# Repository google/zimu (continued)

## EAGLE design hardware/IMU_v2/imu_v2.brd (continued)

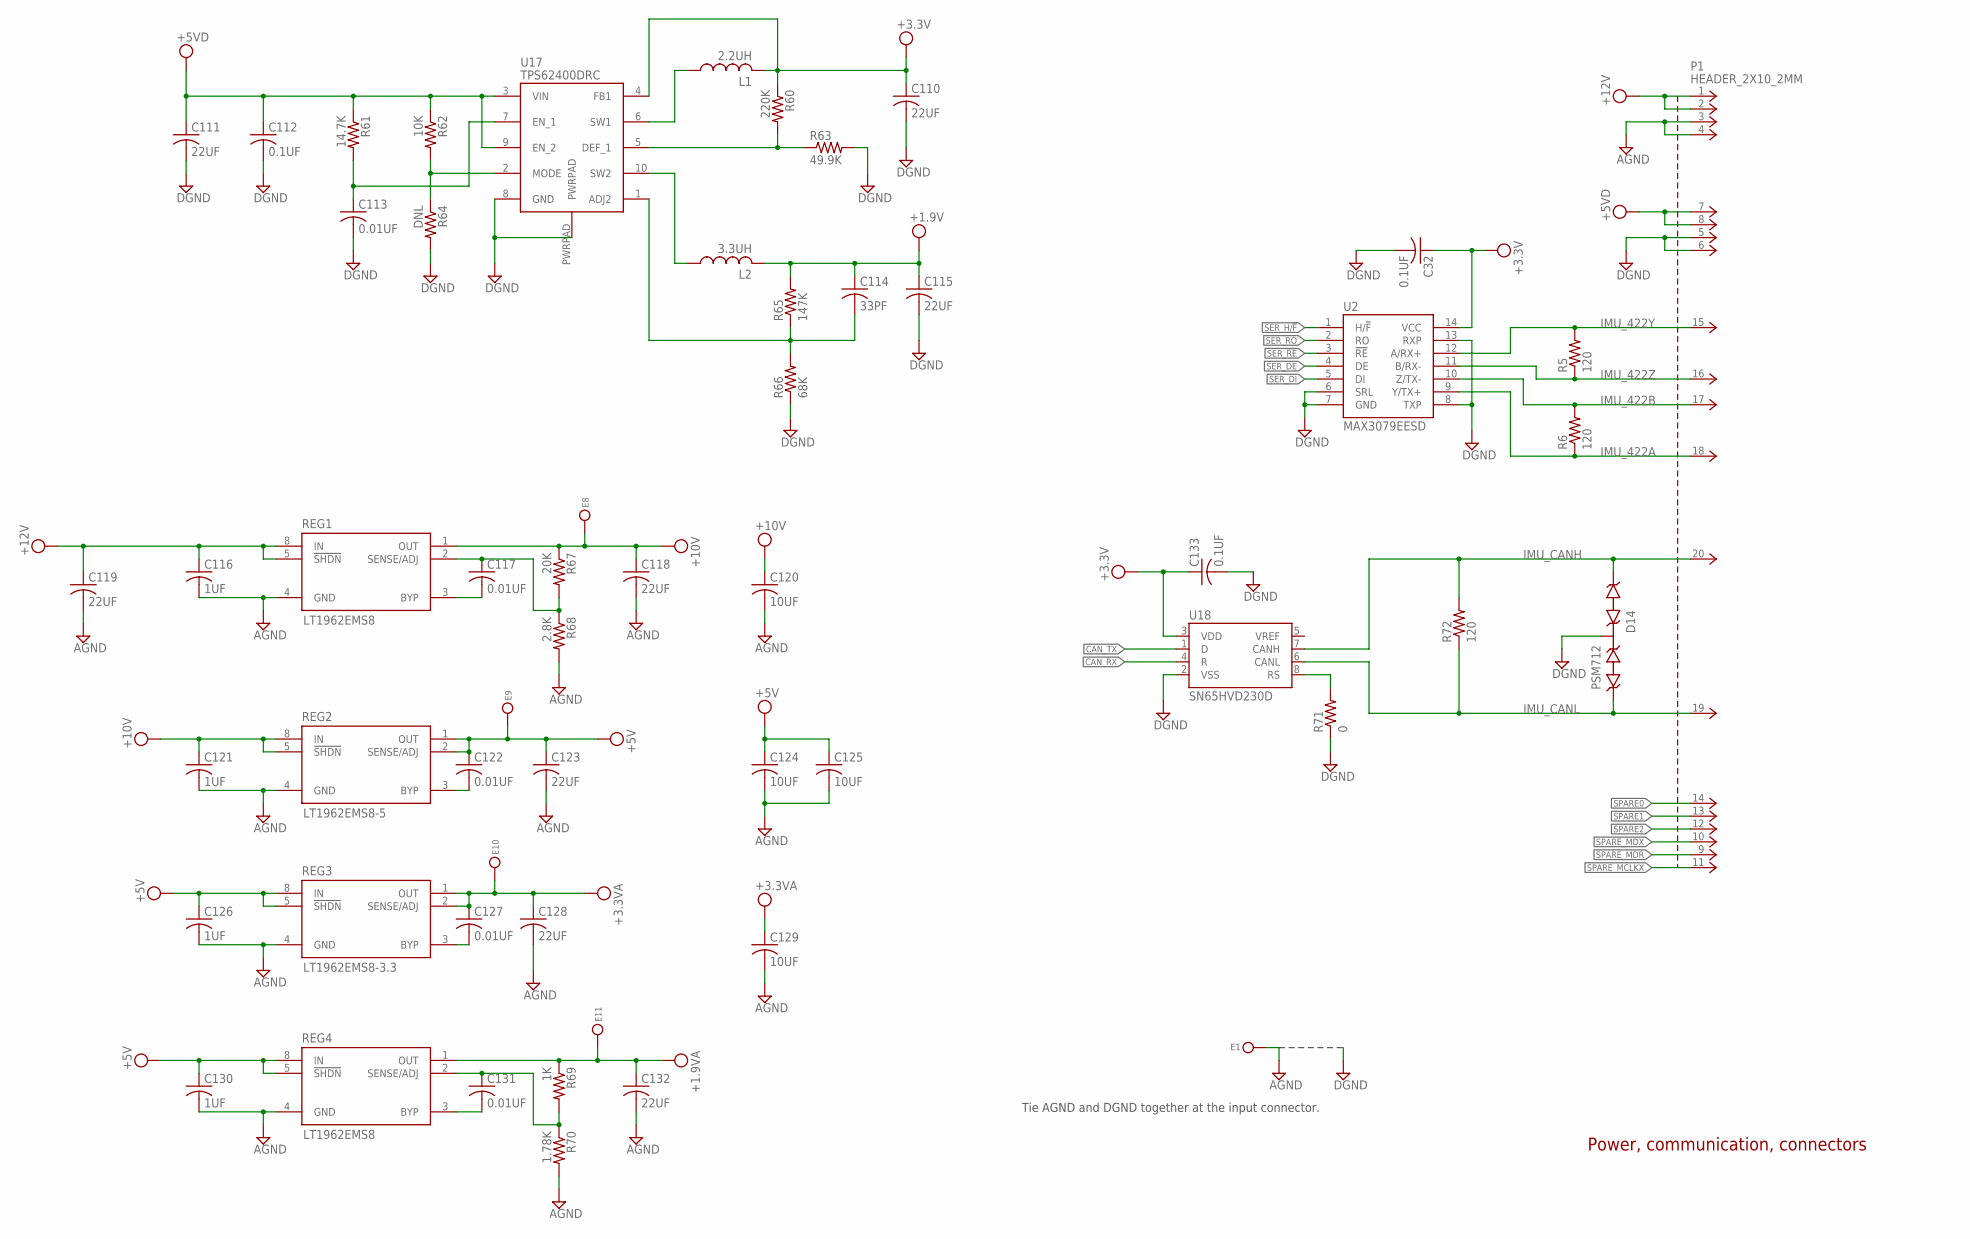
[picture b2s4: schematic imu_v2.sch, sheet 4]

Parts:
C32, C112, C133: 0.1UF; C0603K
C110, C111, C115, C118, C119, C123, C128, C132: 22UF; C1210K
C113, C117, C122, C127, C131: 0.01UF; C0603K
C114: 33PF; C0603K
C116, C121, C126, C130: 1UF; C0603K
C120, C124, C125, C129: 10UF; C1206K
D14: PSM712; SOT23
E1: 5015_TESTCLIP
E8, E9, E10, E11: TP30
L1: 2.2UH; VLF3010A
L2: 3.3UH; VLF3010A
P1: HEADER_2X10_2MM
R5, R6, R72: 120; R0603
R60: 220K; R0603
R61: 14.7K; R0603
R62: 10K; R0603
R63: 49.9K; R0603
R64: DNL; R0603
R65: 147K; R0603
R66: 68K; R0603
R67: 20K; R0603
R68: 2.8K; R0603
R69: 1K; R0603
R70: 1.78K; R0603
R71: 0; R0603
REG1, REG4: LT1962EMS8; MSOP8
REG2: LT1962EMS8-5; MSOP8
REG3: LT1962EMS8-3.3; MSOP8
U2: MAX3079EESD; SOIC14-NARROW
U17: TPS62400DRC; QFN10
U18: SN65HVD230D; SO08

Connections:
+1.9V: C114.1, C115.1, L2.2, R65.2; also elsewhere on the board
+1.9VA: C132.1, E11.1, R69.1, REG4.1 (OUT); also elsewhere on the board
+3.3V: C32.1, C110.1, C133.1, L1.2, R60.1, U2.14 (VCC), U17.4 (FB1), U18.3 (VDD); also elsewhere on the board
+3.3VA: C127.1, C128.1, C129.1, E10.1, REG3.1 (OUT), REG3.2 (SENSE/ADJ); also elsewhere on the board
+5V: C122.1, C123.1, C124.1, C125.1, C126.1, C130.1, E9.1, REG2.1 (OUT), REG2.2 (SENSE/ADJ), REG3.5 (!SHDN), REG3.8 (IN), REG4.5 (!SHDN), REG4.8 (IN); also elsewhere on the board
+5VD: C111.1, C112.1, P1.7, P1.8, R61.1, R62.1, U17.3 (VIN), U17.9 (EN_2)
+10V: C118.1, C120.1, C121.1, E8.1, R67.1, REG1.1 (OUT), REG2.5 (!SHDN), REG2.8 (IN); also elsewhere on the board
+12V: C116.1, C119.1, P1.1, P1.2, REG1.5 (!SHDN), REG1.8 (IN)
AGND: C116.2, C118.2, C119.2, C120.2, C121.2, C123.2, C124.2, C125.2, C126.2, C128.2, C129.2, C130.2, C132.2, E1.1, P1.3, P1.4, R68.2, R70.2, REG1.4 (GND), REG2.4 (GND), REG3.4 (GND), REG4.4 (GND); also elsewhere on the board
CAN_RX: U18.4 (R); also elsewhere on the board
CAN_TX: U18.1 (D); also elsewhere on the board
DGND: C32.2, C110.2, C111.2, C112.2, C113.2, C115.2, C133.2, D14.3, P1.5, P1.6, R63.2, R64.2, R66.1, R71.1, U2.6 (SRL), U2.7 (GND), U2.8 (TXP), U2.13 (RXP), U17.8 (GND), U17.PWRPAD, U18.2 (VSS); also elsewhere on the board
IMU_422A: P1.18, R6.1, U2.9 (Y/TX+)
IMU_422B: P1.17, R6.2, U2.10 (Z/TX-)
IMU_422Y: P1.15, R5.2, U2.12 (A/RX+)
IMU_422Z: P1.16, R5.1, U2.11 (B/RX-)
IMU_CANH: D14.1, P1.20, R72.2, U18.7 (CANH)
IMU_CANL: D14.2, P1.19, R72.1, U18.6 (CANL)
unnamed: R71.2, U18.8 (RS)
unnamed: C122.2, REG2.3 (BYP)
unnamed: C127.2, REG3.3 (BYP)
unnamed: C117.2, REG1.3 (BYP)
unnamed: C117.1, R67.2, R68.1, REG1.2 (SENSE/ADJ)
unnamed: C131.2, REG4.3 (BYP)
unnamed: C131.1, R69.2, R70.1, REG4.2 (SENSE/ADJ)
unnamed: L1.1, U17.6 (SW1)
unnamed: L2.1, U17.10 (SW2)
unnamed: R60.2, R63.1, U17.5 (DEF_1)
unnamed: R62.2, R64.1, U17.2 (MODE)
unnamed: C114.2, R65.1, R66.2, U17.1 (ADJ2)
unnamed: C113.1, R61.2, U17.7 (EN_1)
SER_!RE: U2.3 (!RE); also elsewhere on the board
SER_DE: U2.4 (DE); also elsewhere on the board
SER_DI: U2.5 (DI); also elsewhere on the board
SER_H/!F: U2.1 (H/!F); also elsewhere on the board
SER_RO: U2.2 (RO); also elsewhere on the board
SPARE0: P1.14; also elsewhere on the board
SPARE1: P1.13; also elsewhere on the board
SPARE2: P1.12; also elsewhere on the board
SPARE_MCLKX: P1.11; also elsewhere on the board
SPARE_MDR: P1.9; also elsewhere on the board
SPARE_MDX: P1.10; also elsewhere on the board

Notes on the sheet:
Power, communication, connectors
Tie AGND and DGND together at the input connector.

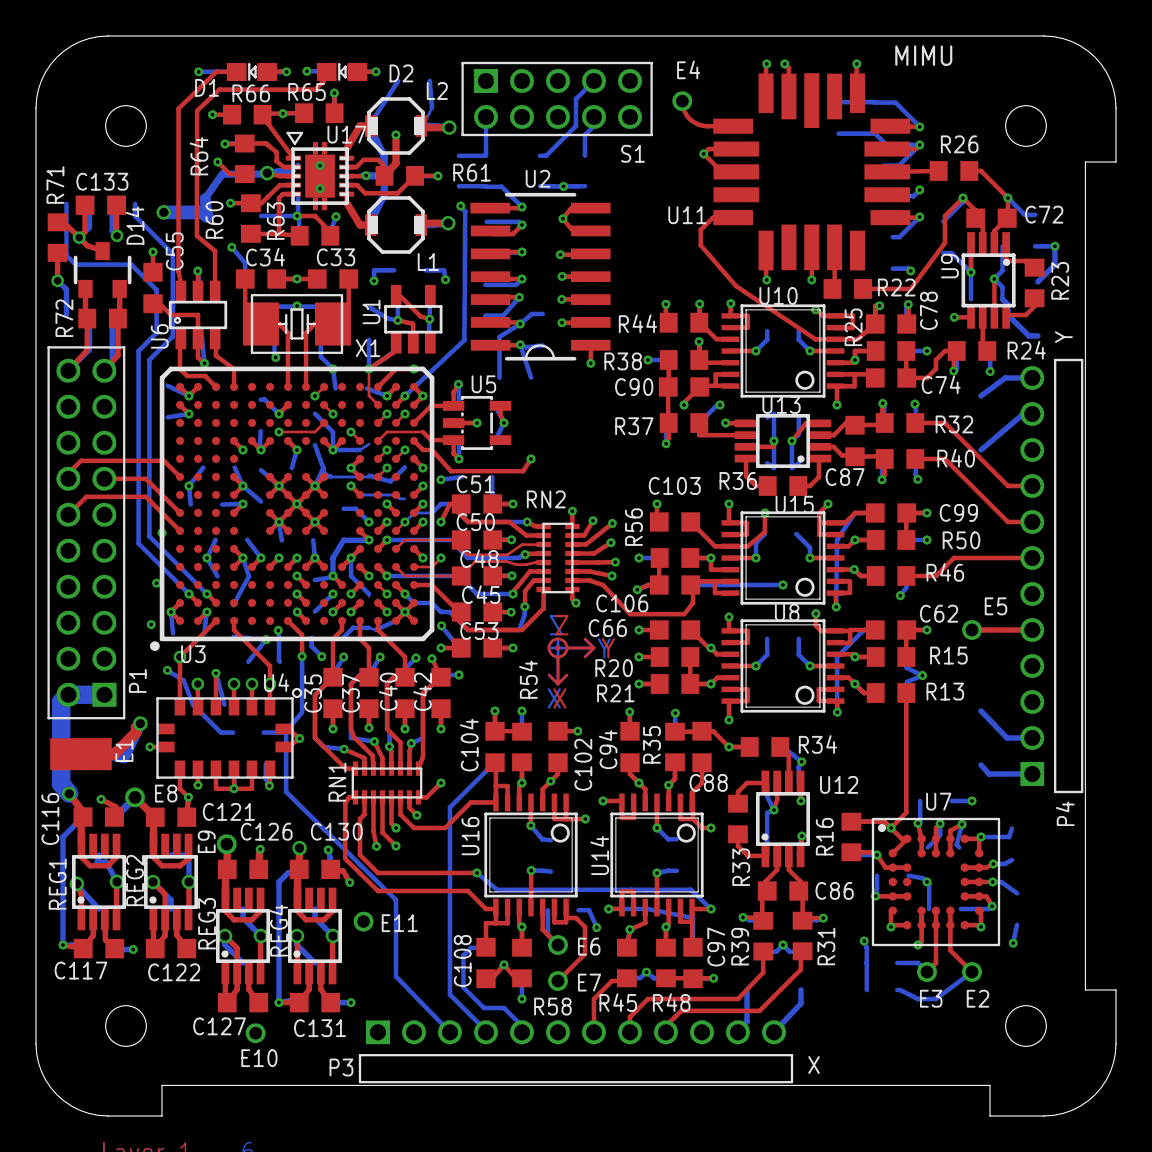
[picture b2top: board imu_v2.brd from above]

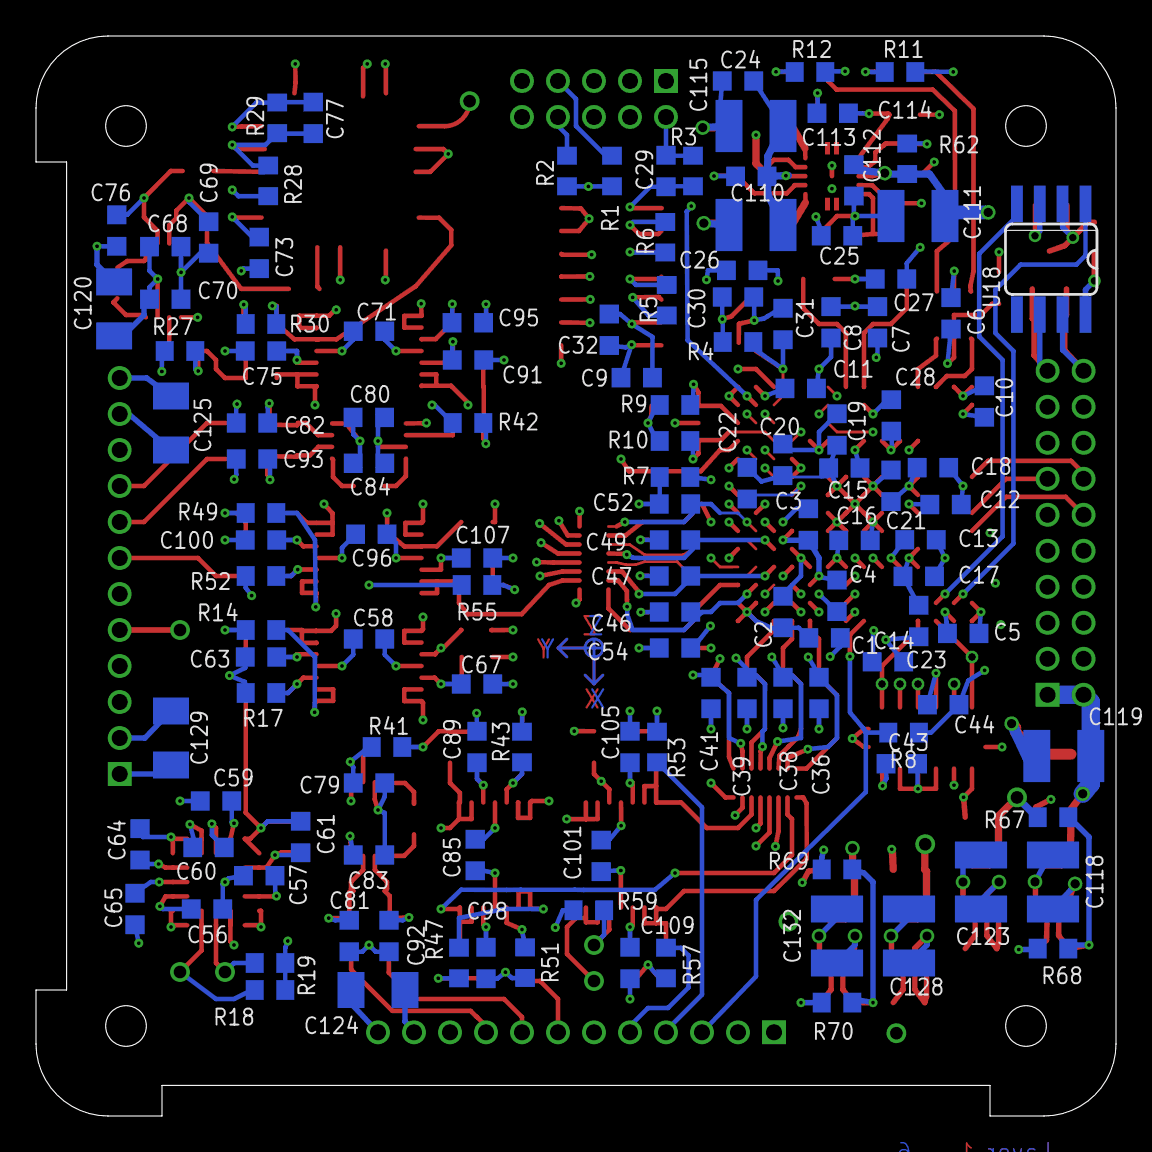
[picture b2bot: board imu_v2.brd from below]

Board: 6 copper layers, 60.0 x 60.0 mm, 250 parts (132 on the bottom side), 172 nets.

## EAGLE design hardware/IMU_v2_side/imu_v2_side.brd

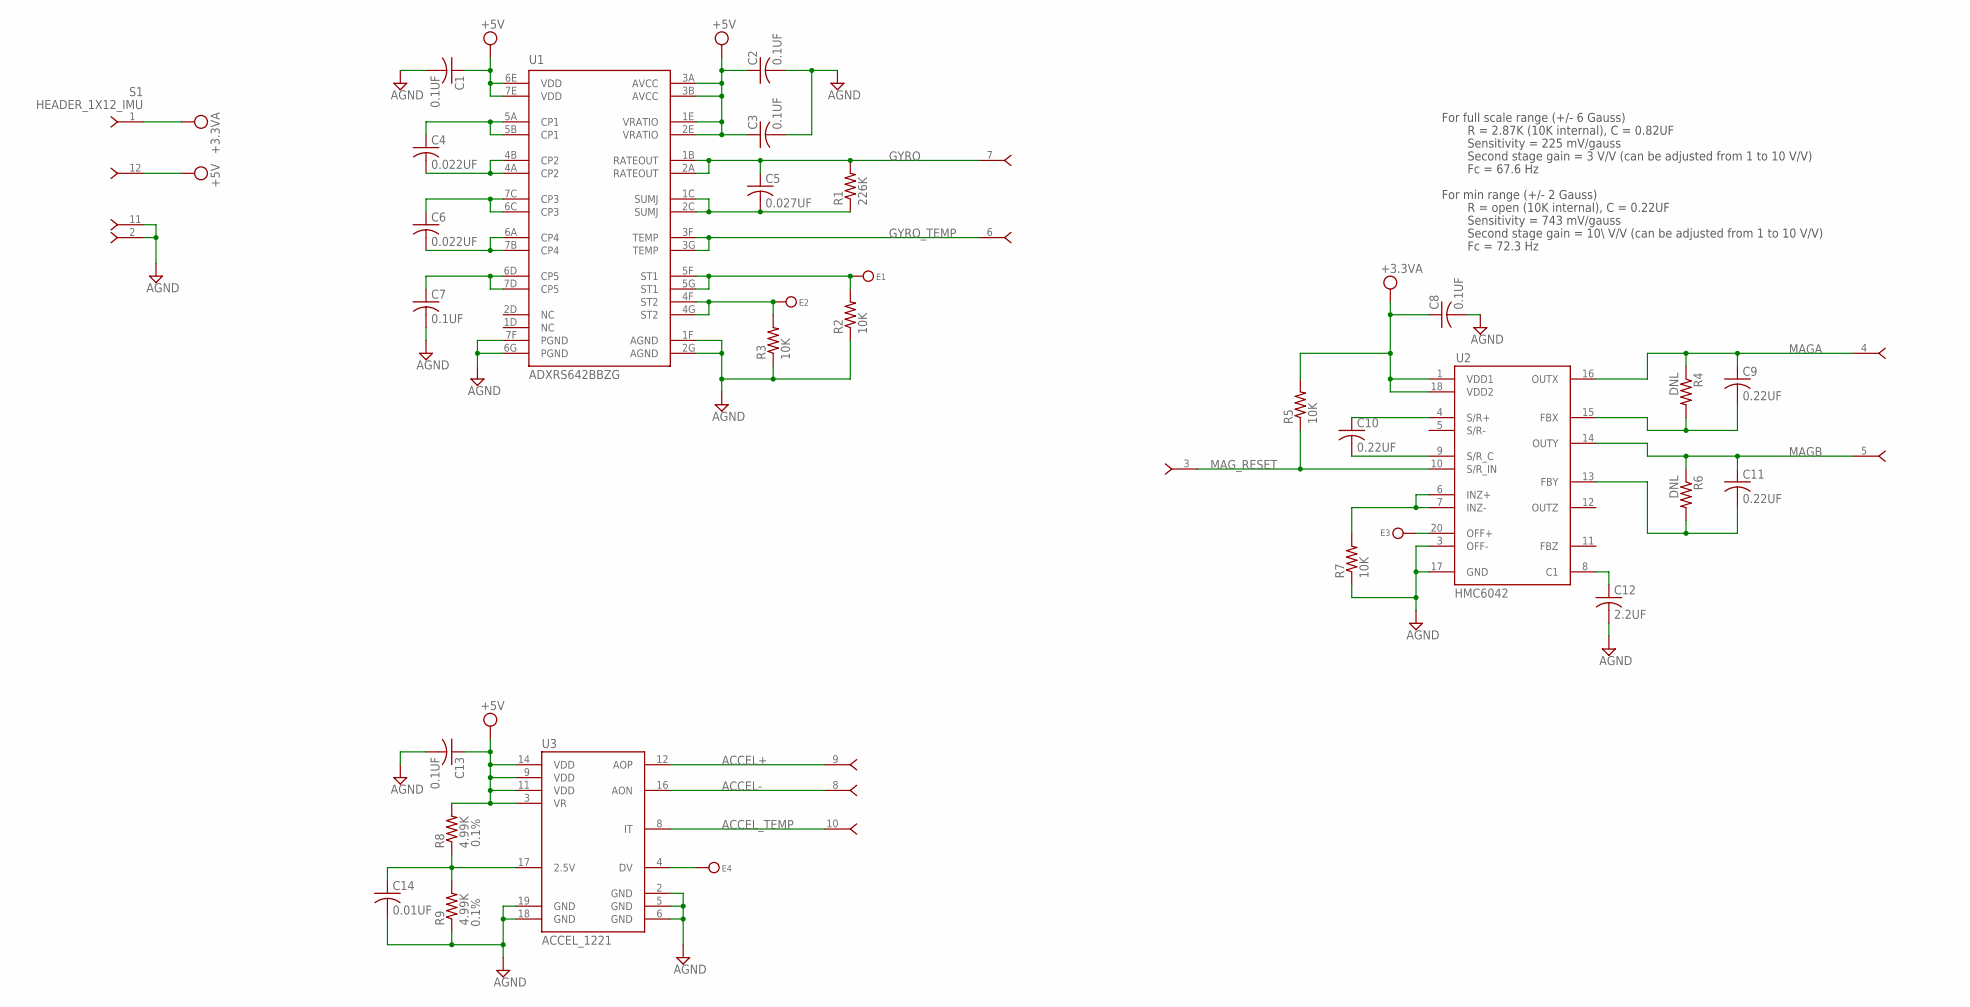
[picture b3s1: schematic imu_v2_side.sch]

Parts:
C1, C2, C3, C7, C8, C13: 0.1UF; C0603K
C4, C6: 0.022UF; C0603K
C5: 0.027UF; C0603K
C9, C10, C11: 0.22UF; C0603K
C12: 2.2UF; C0603K
C14: 0.01UF; C0603K
E1, E2, E3, E4: TP30
R1: 226K; R0603
R2, R3, R5, R7: 10K; R0603
R4, R6: DNL; R0603
R8, R9: 4.99K; R0603
S1: HEADER_1X12_IMU; HEADER_1X12_2MM_TH
U1: ADXRS642BBZG; ADXRS_CBGA32
U2: HMC6042; HMC6042_LPCC
U3: ACCEL_1221; 1221_LCC

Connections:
+3.3VA: C8.1, R5.2, S1.1, U2.1 (VDD1), U2.18 (VDD2)
+5V: C1.1, C2.1, C3.1, C13.1, R8.2, S1.12 (1), U1.1E (VRATIO), U1.2E (VRATIO), U1.3A (AVCC), U1.3B (AVCC), U1.6E (VDD), U1.7E (VDD), U3.3 (VR), U3.9 (VDD), U3.11 (VDD), U3.14 (VDD)
ACCEL+: S1.9 (1), U3.12 (AOP)
ACCEL-: S1.8 (1), U3.16 (AON)
ACCEL_TEMP: S1.10 (1), U3.8 (IT)
AGND: C1.2, C2.2, C3.2, C7.2, C8.2, C12.2, C13.2, C14.2, R2.1, R3.1, R7.1, R9.1, S1.2 (1), S1.11 (1), U1.1F (AGND), U1.2G (AGND), U1.6G (PGND), U1.7F (PGND), U2.3 (OFF-), U2.17 (GND), U3.2 (GND), U3.5 (GND), U3.6 (GND), U3.18 (GND), U3.19 (GND)
GYRO: C5.1, R1.2, S1.7 (1), U1.1B (RATEOUT), U1.2A (RATEOUT)
GYRO_ST1: E1.1, R2.2, U1.5F (ST1), U1.5G (ST1)
GYRO_ST2: E2.1, R3.2, U1.4F (ST2), U1.4G (ST2)
GYRO_TEMP: S1.6 (1), U1.3F (TEMP), U1.3G (TEMP)
MAGA: C9.1, R4.1, S1.4 (1), U2.16 (OUTX)
MAGB: C11.1, R6.1, S1.5 (1), U2.14 (OUTY)
MAG_RESET: R5.1, S1.3 (1), U2.10 (S/R_IN)
unnamed: C4.1, U1.5A (CP1), U1.5B (CP1)
unnamed: C4.2, U1.4A (CP2), U1.4B (CP2)
unnamed: C6.1, U1.6C (CP3), U1.7C (CP3)
unnamed: C6.2, U1.6A (CP4), U1.7B (CP4)
unnamed: C7.1, U1.6D (CP5), U1.7D (CP5)
unnamed: C14.1, R8.1, R9.2, U3.17 (2.5V)
unnamed: C5.2, R1.1, U1.1C (SUMJ), U1.2C (SUMJ)
unnamed: E4.1, U3.4 (DV)
unnamed: E3.1, U2.20 (OFF+)
unnamed: R7.2, U2.6 (INZ+), U2.7 (INZ-)
unnamed: C10.1, U2.4 (S/R+)
unnamed: C10.2, U2.9 (S/R_C)
unnamed: C12.1, U2.8 (C1)
unnamed: C9.2, R4.2, U2.15 (FBX)
unnamed: C11.2, R6.2, U2.13 (FBY)

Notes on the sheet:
Second stage gain = 3 V/V (can be adjusted from 1 to 10 V/V)
Sensitivity = 225 mV/gauss
Fc = 67.6 Hz
For full scale range (+/- 6 Gauss)
For min range (+/- 2 Gauss)
R = 2.87K (10K internal), C = 0.82UF
Second stage gain = 10\ V/V (can be adjusted from 1 to 10 V/V)
Sensitivity = 743 mV/gauss
Fc = 72.3 Hz
R = open (10K internal), C = 0.22UF

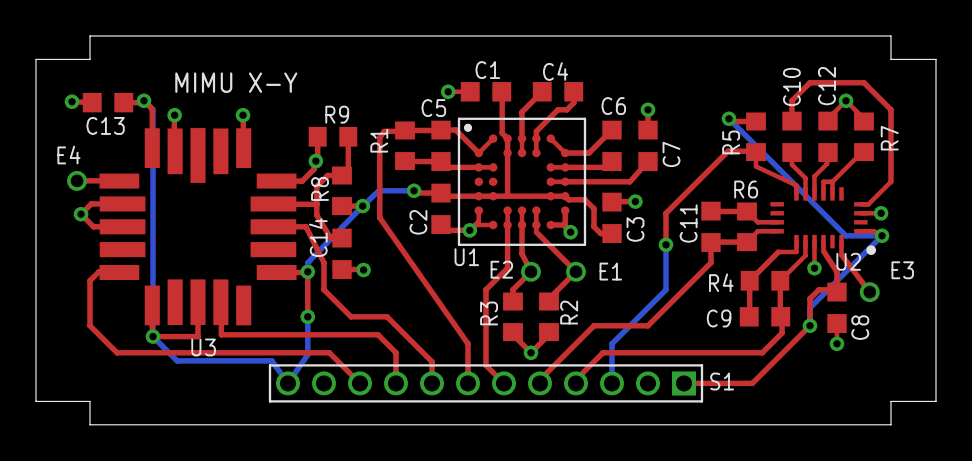
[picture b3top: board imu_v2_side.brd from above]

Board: 2 copper layers, 50.0 x 21.6 mm, 31 parts (0 on the bottom side), 28 nets.

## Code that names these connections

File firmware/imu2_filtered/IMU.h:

/*
Copyright 2013 Google Inc. All Rights Reserved.

Licensed under the Apache License, Version 2.0 (the "License");
you may not use this file except in compliance with the License.
You may obtain a copy of the License at

   http://www.apache.org/licenses/LICENSE-2.0

Unless required by applicable law or agreed to in writing, software
distributed under the License is distributed on an "AS IS" BASIS,
WITHOUT WARRANTIES OR CONDITIONS OF ANY KIND, either express or implied.
See the License for the specific language governing permissions and
limitations under the License.
*/

// IMU header file (imu.h)

#include "DSP2833x_Device.h"
#include <string.h>

// Board specific calibration info
#include "cal_null.h"
//#include "../calibration/IMU10_20120604T1806.h"

#define CPU_CLOCK_SPEED 6.667L   // for a 150MHz CPU clock speed
#define DELAY_US(A) DSP28x_usDelay(((((long double) A * 1000.0L) /
        (long double)CPU_CLOCK_SPEED) - 9.0L) / 5.0L)
extern void DSP28x_usDelay(unsigned long Count);

// Pin definitions (A: 0-31, B: 32-63, C: 64-79)
#define SER_DI GPIO22
#define SER_RO GPIO23
#define SER_nRE GPIO24
#define SER_DE GPIO25
#define SER_HnF GPIO26

#define ACCEL3_CS GPIO29
#define ACCEL3_SPC GPIO56
#define ACCEL3_SDI GPIO54
#define ACCEL3_SDO GPIO55
#define ACCEL3_RDYINT GPIO0

#define ID_SDA GPIO32
#define ID_SCL GPIO33

#define MAG_RESET GPIO9

#define nLED0 GPIO70
#define nLED1 GPIO67

#define SPARE0 GPIO34
#define SPARE1 GPIO41
#define SPARE2 GPIO44
#define SPARE_MDX GPIO12
#define SPARE_MDR GPIO13
#define SPARE_MCLKX GPIO14

#define LED1_PATTERN 0xA6A6A6A6

// Used to set the output rate during debug mode.  This has no impact on the
// filter decimation rate.
#define OVERSAMPLE_RATE 4

typedef struct IMURawData_t {
  // Raw Sensor reading
  Uint16 accel_x;
  Uint16 accel_y;
  Uint16 accel_z;
  Uint16 gyro_x;
  Uint16 gyro_y;
  Uint16 gyro_z;
  Uint16 mag_x;
  Uint16 mag_y;
  Uint16 mag_z;

  // Temperatures
  Uint16 accel_x_t;
  Uint16 accel_y_t;
  Uint16 accel_z_t;
  Uint16 gyro_x_t;
  Uint16 gyro_y_t;
  Uint16 gyro_z_t;

  // Voltage Reference
  Uint16 ref_mon;

  // 3-Axis Readings
  int16 accel3_x;
  int16 accel3_y;
  int16 accel3_z;

  // Serial Number
  Uint64 serial_id;
} IMURawData;

extern IMURawData rawData;

typedef struct IMUConvData_t {

  float accel_x;
  float accel_y;
  float accel_z;
  float gyro_x;
  float gyro_y;
  float gyro_z;
  float mag_x;
  float mag_y;
  float mag_z;

  float accel3_x;
  float accel3_y;
  float accel3_z;

  float ref_mon;
} IMUConvData;

extern IMUConvData convData;

typedef struct IMUFilterData_t {

  float accel_x;
  float accel_y;
  float accel_z;
  float gyro_x;
  float gyro_y;
  float gyro_z;

} IMUFilterData;

extern IMUFilterData filterData;
extern IMUFilterData filterInputData;

extern char debug_mode;
